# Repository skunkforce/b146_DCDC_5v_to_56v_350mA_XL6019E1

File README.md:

# edgy_board number b146
This design is part of the [edgy board project](https://github.com/skunkforce/edgy_boards).

# getting started
This repository uses submodules. After cloning use the command 

```$ git submodule update --init --recursive```

to pull the submodules before opening the project with kicad. 

# Tests
Tests can be found in [TESTS.md](TESTS.md)

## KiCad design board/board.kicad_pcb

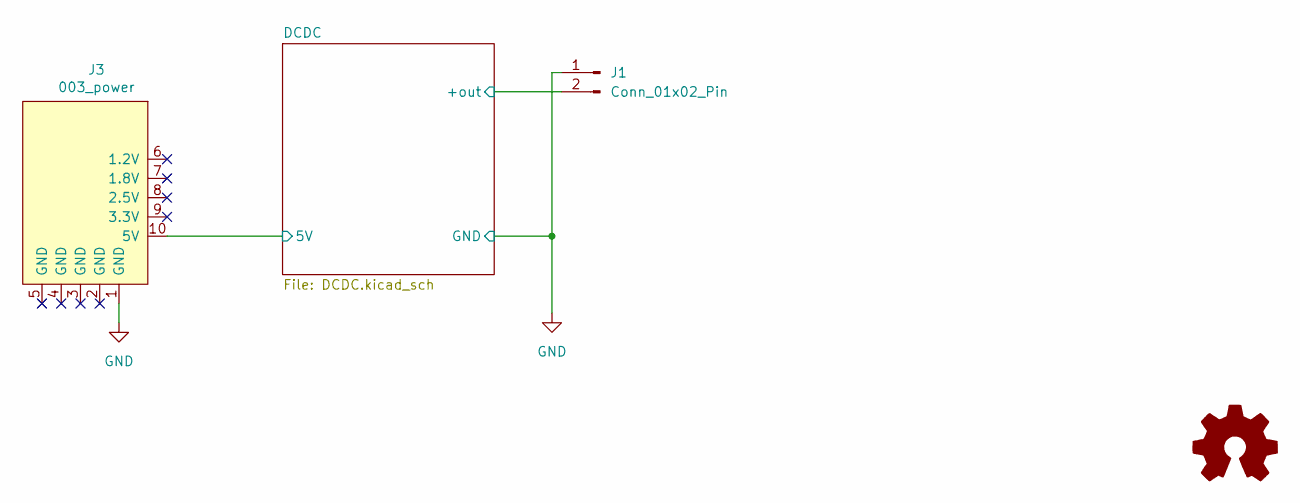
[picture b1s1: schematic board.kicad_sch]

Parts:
J1: Conn_01x02_Pin; PinHeader_1x02_P2.54mm_Vertical
J3: 003_power; on_edge_2x05_device
LOGO1: Logo_Open_Hardware_Small; OSHW-Symbol_6.7x6mm_SilkScreen

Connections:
/DCDC/5V: J3.10 (5V); also elsewhere on the board
/DCDC/+out: J1.2; also elsewhere on the board
GND: J1.1, J3.1 (GND); also elsewhere on the board

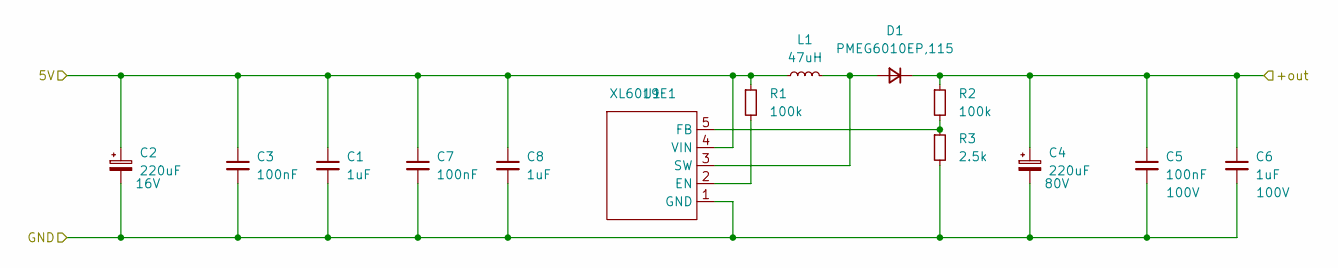
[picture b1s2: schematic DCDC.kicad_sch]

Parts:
C1, C8: 1uF; C_0603_1608Metric
C2: 220uF; CP_Elec_10x14.3; Voltage 16V
C3, C7: 100nF; C_0603_1608Metric
C4: 220uF; CP_Elec_10x14.3; Voltage 80V; MPN VKME1651K221MV
C5: 100nF; C_0603_1608Metric; Voltage 100V
C6: 1uF; C_1206_3216Metric; Voltage 100V
D1: PMEG6010EP,115; D_SOD-128
L1: 47uH; L_Sunlord_MWSA1206S-470; MPN YSPI1365-470M
R1, R2: 100k; R_0603_1608Metric
R3: 2.5k; R_0603_1608Metric
U1: XL6019E1; TO-263-5_TabPin3

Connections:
/DCDC/5V: C1.1, C2.1, C3.1, C7.1, C8.1, L1.1, R1.1, U1.4 (VIN); also elsewhere on the board
/DCDC/+out: C4.1, C5.1, C6.1, D1.1 (K), R2.1; also elsewhere on the board
GND: C1.2, C2.2, C3.2, C4.2, C5.2, C6.2, C7.2, C8.2, R3.2, U1.1 (GND); also elsewhere on the board
unnamed: D1.2 (A), L1.2, U1.3 (SW)
unnamed: R1.2, U1.2 (EN)
unnamed: R2.2, R3.1, U1.5 (FB)

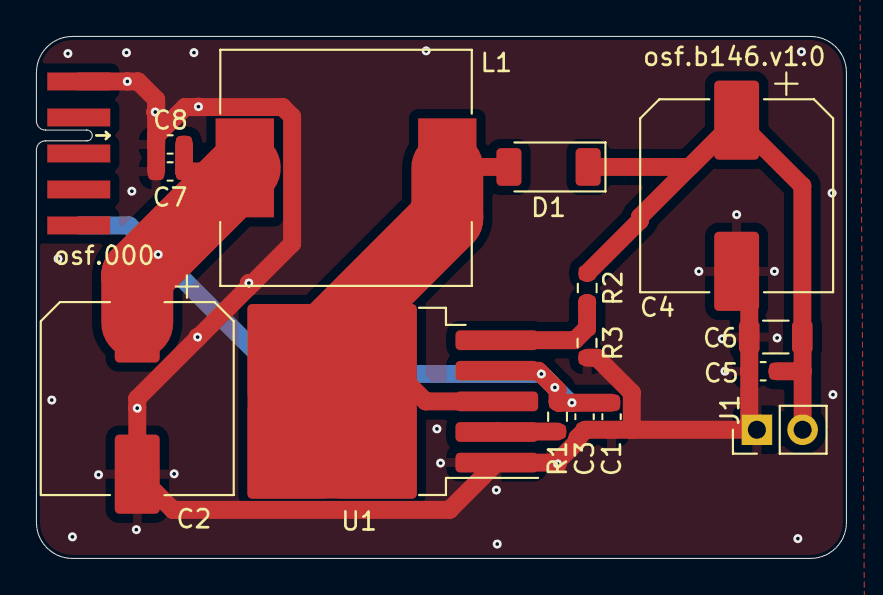
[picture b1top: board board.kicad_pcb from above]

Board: 2 copper layers, 45.0 x 29.0 mm, 17 parts (1 on the bottom side), 6 nets.

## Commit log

2024-01-14 initial b146
